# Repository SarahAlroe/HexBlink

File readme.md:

# HexBlink

A hexagonal circuit board designed for 5mm blink or flicker LEDs with dedicated SMD resistors.  
More info can be found [here](http://sarah.alroe.dk/2021/HexBlink/)

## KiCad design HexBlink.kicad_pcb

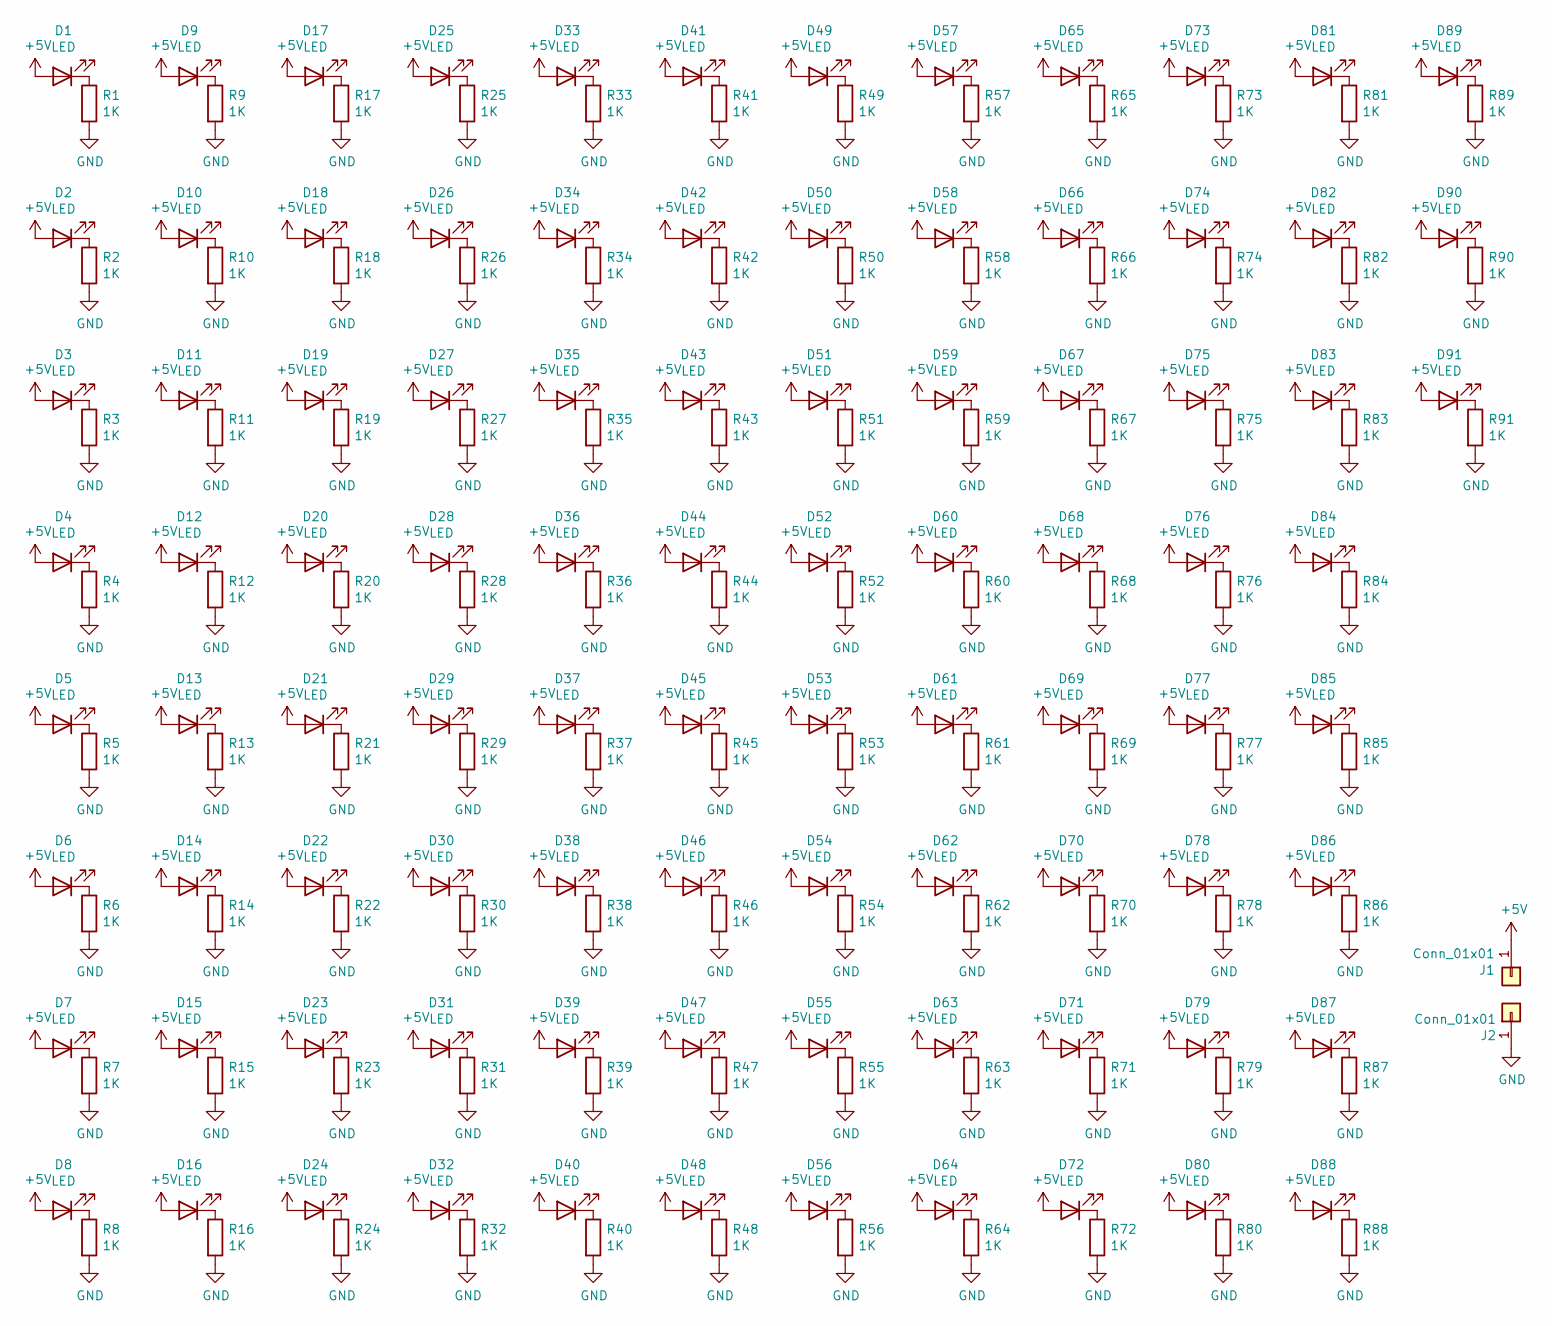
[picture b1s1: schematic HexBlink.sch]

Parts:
D1, D2, D3, D4, D5, D6, D7, D8, D9, D10, D11, D12, D13, D14, D15, D16, D17, D18, D19, D20, D21, D22, D23, D24, D25, D26, D27, D28, D29, D30, D31, D32, D33, D34, D35, D36, D37, D38, D39, D40, D41, D42, D43, D44, D45, D46, D47, D48, D49, D50, D51, D52, D53, D54, D55, D56, D57, D58, D59, D60, D61, D62, D63, D64, D65, D66, D67, D68, D69, D70, D71, D72, D73, D74, D75, D76, D77, D78, D79, D80, D81, D82, D83, D84, D85, D86, D87, D88, D89, D90, D91: LED; LED_D5.0mm_Clear
J1, J2: Conn_01x01; Pin_D1.0mm_L10.0mm
R1, R2, R3, R4, R5, R6, R7, R8, R9, R10, R11, R12, R13, R14, R15, R16, R17, R18, R19, R20, R21, R22, R23, R24, R25, R26, R27, R28, R29, R30, R31, R32, R33, R34, R35, R36, R37, R38, R39, R40, R41, R42, R43, R44, R45, R46, R47, R48, R49, R50, R51, R52, R53, R54, R55, R56, R57, R58, R59, R60, R61, R62, R63, R64, R65, R66, R67, R68, R69, R70, R71, R72, R73, R74, R75, R76, R77, R78, R79, R80, R81, R82, R83, R84, R85, R86, R87, R88, R89, R90, R91: 1K; R_1206_3216Metric

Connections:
+5V: D1.2 (A), D2.2 (A), D3.2 (A), D4.2 (A), D5.2 (A), D6.2 (A), D7.2 (A), D8.2 (A), D9.2 (A), D10.2 (A), D11.2 (A), D12.2 (A), D13.2 (A), D14.2 (A), D15.2 (A), D16.2 (A), D17.2 (A), D18.2 (A), D19.2 (A), D20.2 (A), D21.2 (A), D22.2 (A), D23.2 (A), D24.2 (A), D25.2 (A), D26.2 (A), D27.2 (A), D28.2 (A), D29.2 (A), D30.2 (A), D31.2 (A), D32.2 (A), D33.2 (A), D34.2 (A), D35.2 (A), D36.2 (A), D37.2 (A), D38.2 (A), D39.2 (A), D40.2 (A), D41.2 (A), D42.2 (A), D43.2 (A), D44.2 (A), D45.2 (A), D46.2 (A), D47.2 (A), D48.2 (A), D49.2 (A), D50.2 (A), D51.2 (A), D52.2 (A), D53.2 (A), D54.2 (A), D55.2 (A), D56.2 (A), D57.2 (A), D58.2 (A), D59.2 (A), D60.2 (A), D61.2 (A), D62.2 (A), D63.2 (A), D64.2 (A), D65.2 (A), D66.2 (A), D67.2 (A), D68.2 (A), D69.2 (A), D70.2 (A), D71.2 (A), D72.2 (A), D73.2 (A), D74.2 (A), D75.2 (A), D76.2 (A), D77.2 (A), D78.2 (A), D79.2 (A), D80.2 (A), D81.2 (A), D82.2 (A), D83.2 (A), D84.2 (A), D85.2 (A), D86.2 (A), D87.2 (A), D88.2 (A), D89.2 (A), D90.2 (A), D91.2 (A), J1.1
GND: J2.1, R1.2, R2.2, R3.2, R4.2, R5.2, R6.2, R7.2, R8.2, R9.2, R10.2, R11.2, R12.2, R13.2, R14.2, R15.2, R16.2, R17.2, R18.2, R19.2, R20.2, R21.2, R22.2, R23.2, R24.2, R25.2, R26.2, R27.2, R28.2, R29.2, R30.2, R31.2, R32.2, R33.2, R34.2, R35.2, R36.2, R37.2, R38.2, R39.2, R40.2, R41.2, R42.2, R43.2, R44.2, R45.2, R46.2, R47.2, R48.2, R49.2, R50.2, R51.2, R52.2, R53.2, R54.2, R55.2, R56.2, R57.2, R58.2, R59.2, R60.2, R61.2, R62.2, R63.2, R64.2, R65.2, R66.2, R67.2, R68.2, R69.2, R70.2, R71.2, R72.2, R73.2, R74.2, R75.2, R76.2, R77.2, R78.2, R79.2, R80.2, R81.2, R82.2, R83.2, R84.2, R85.2, R86.2, R87.2, R88.2, R89.2, R90.2, R91.2
unnamed: D1.1 (K), R1.1
unnamed: D2.1 (K), R2.1
unnamed: D3.1 (K), R3.1
unnamed: D4.1 (K), R4.1
unnamed: D5.1 (K), R5.1
unnamed: D6.1 (K), R6.1
unnamed: D7.1 (K), R7.1
unnamed: D8.1 (K), R8.1
unnamed: D9.1 (K), R9.1
unnamed: D10.1 (K), R10.1
unnamed: D11.1 (K), R11.1
unnamed: D12.1 (K), R12.1
unnamed: D13.1 (K), R13.1
unnamed: D14.1 (K), R14.1
unnamed: D15.1 (K), R15.1
unnamed: D16.1 (K), R16.1
unnamed: D17.1 (K), R17.1
unnamed: D18.1 (K), R18.1
unnamed: D19.1 (K), R19.1
unnamed: D20.1 (K), R20.1
unnamed: D21.1 (K), R21.1
unnamed: D22.1 (K), R22.1
unnamed: D23.1 (K), R23.1
unnamed: D24.1 (K), R24.1
unnamed: D25.1 (K), R25.1
unnamed: D26.1 (K), R26.1
unnamed: D27.1 (K), R27.1
unnamed: D28.1 (K), R28.1
unnamed: D29.1 (K), R29.1
unnamed: D30.1 (K), R30.1
unnamed: D31.1 (K), R31.1
unnamed: D32.1 (K), R32.1
unnamed: D33.1 (K), R33.1
unnamed: D34.1 (K), R34.1
unnamed: D35.1 (K), R35.1
unnamed: D36.1 (K), R36.1
unnamed: D37.1 (K), R37.1
unnamed: D38.1 (K), R38.1
unnamed: D39.1 (K), R39.1
unnamed: D40.1 (K), R40.1
unnamed: D41.1 (K), R41.1
unnamed: D42.1 (K), R42.1
unnamed: D43.1 (K), R43.1
unnamed: D44.1 (K), R44.1
unnamed: D45.1 (K), R45.1
unnamed: D46.1 (K), R46.1
unnamed: D47.1 (K), R47.1
unnamed: D48.1 (K), R48.1
unnamed: D49.1 (K), R49.1
unnamed: D50.1 (K), R50.1
unnamed: D51.1 (K), R51.1
unnamed: D52.1 (K), R52.1
unnamed: D53.1 (K), R53.1
unnamed: D54.1 (K), R54.1
unnamed: D55.1 (K), R55.1
unnamed: D56.1 (K), R56.1
unnamed: D57.1 (K), R57.1
unnamed: D58.1 (K), R58.1
unnamed: D59.1 (K), R59.1
unnamed: D60.1 (K), R60.1
unnamed: D61.1 (K), R61.1
unnamed: D62.1 (K), R62.1
unnamed: D63.1 (K), R63.1
unnamed: D64.1 (K), R64.1
unnamed: D65.1 (K), R65.1
unnamed: D66.1 (K), R66.1
unnamed: D67.1 (K), R67.1
unnamed: D68.1 (K), R68.1
unnamed: D69.1 (K), R69.1
unnamed: D70.1 (K), R70.1
unnamed: D71.1 (K), R71.1
unnamed: D72.1 (K), R72.1
unnamed: D73.1 (K), R73.1
unnamed: D74.1 (K), R74.1
unnamed: D75.1 (K), R75.1
unnamed: D76.1 (K), R76.1
unnamed: D77.1 (K), R77.1
unnamed: D78.1 (K), R78.1
unnamed: D79.1 (K), R79.1
unnamed: D80.1 (K), R80.1
unnamed: D81.1 (K), R81.1
unnamed: D82.1 (K), R82.1
unnamed: D83.1 (K), R83.1
unnamed: D84.1 (K), R84.1
unnamed: D85.1 (K), R85.1
unnamed: D86.1 (K), R86.1
unnamed: D87.1 (K), R87.1
unnamed: D88.1 (K), R88.1
unnamed: D89.1 (K), R89.1
unnamed: D90.1 (K), R90.1
unnamed: D91.1 (K), R91.1

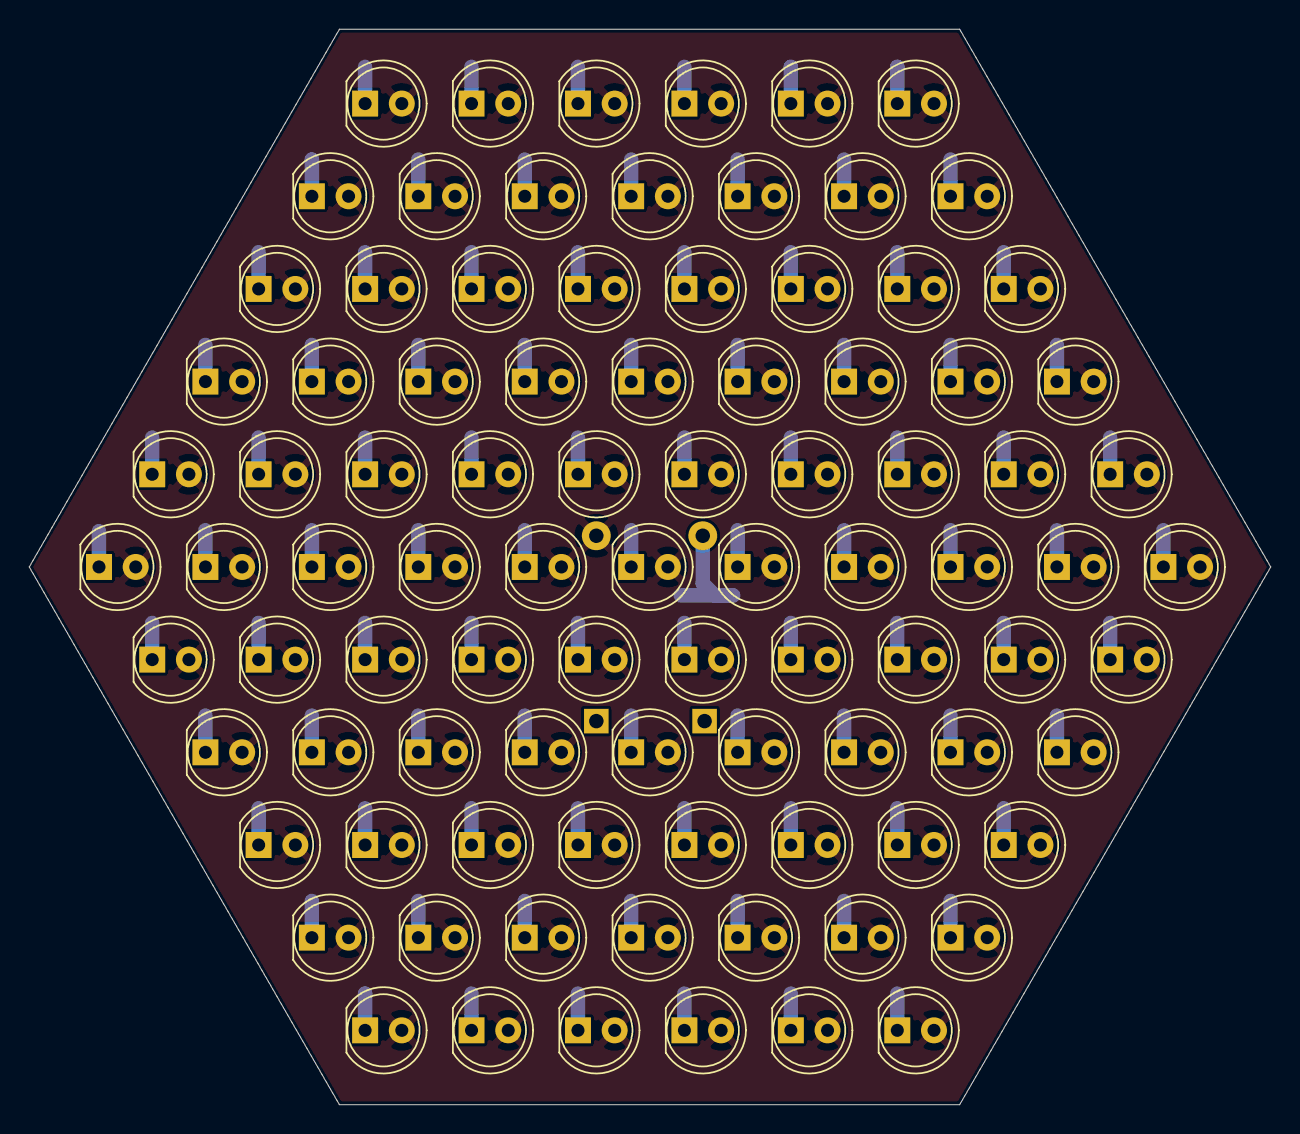
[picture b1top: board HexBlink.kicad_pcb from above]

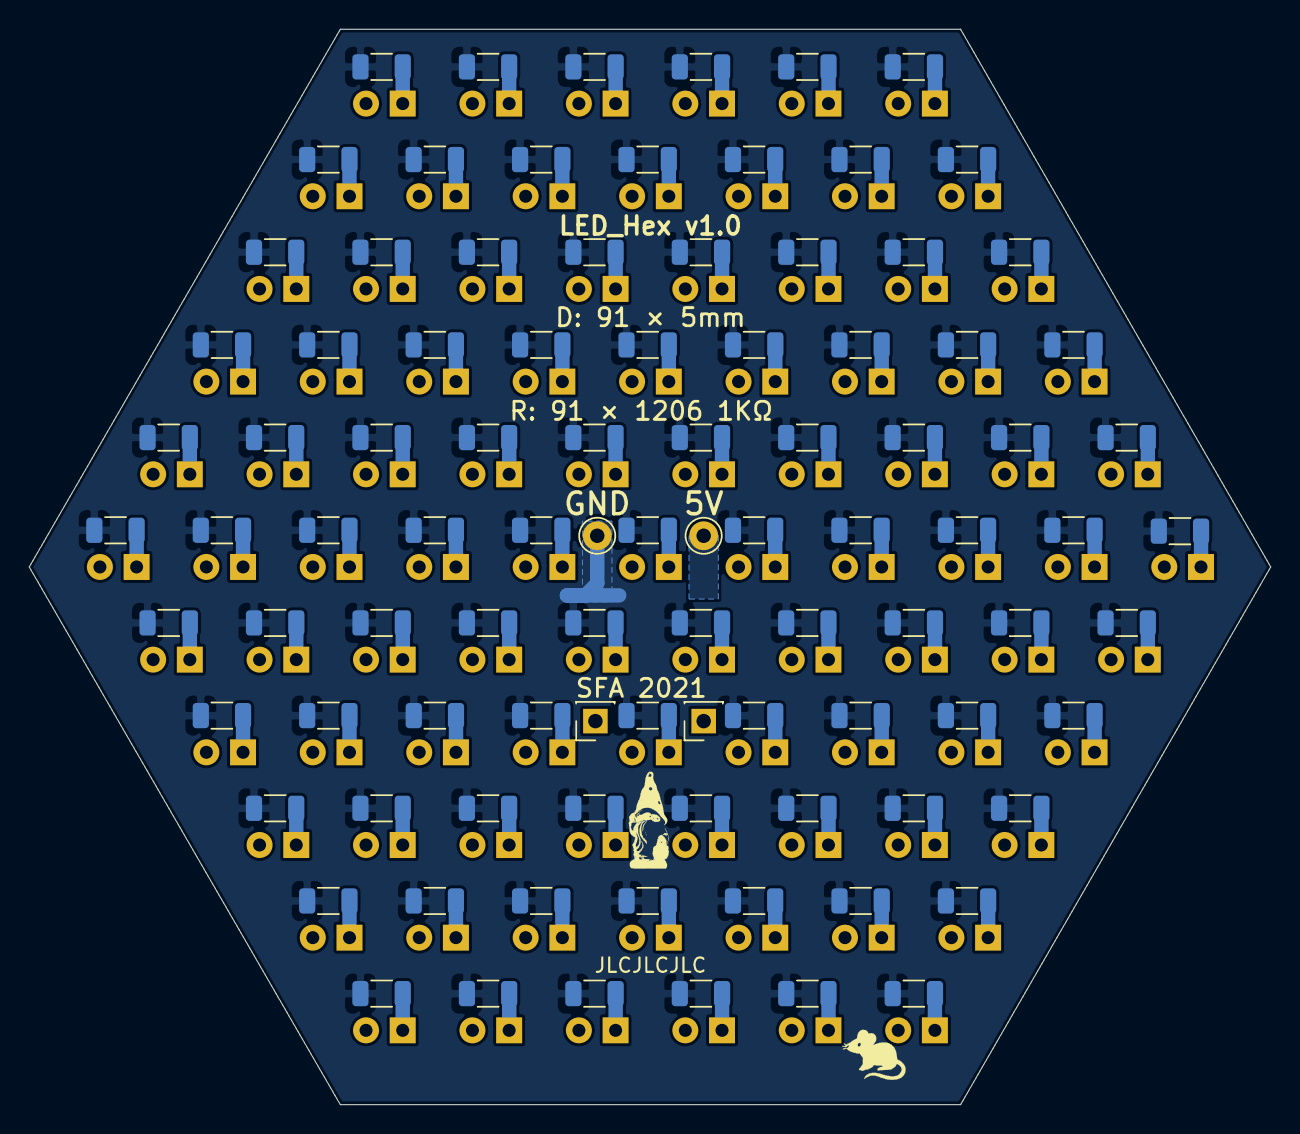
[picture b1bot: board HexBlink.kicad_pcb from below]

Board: 2 copper layers, 85.9 x 74.4 mm, 184 parts (93 on the bottom side), 93 nets.

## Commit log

2021-08-04 Init
2021-08-04 Added readme
